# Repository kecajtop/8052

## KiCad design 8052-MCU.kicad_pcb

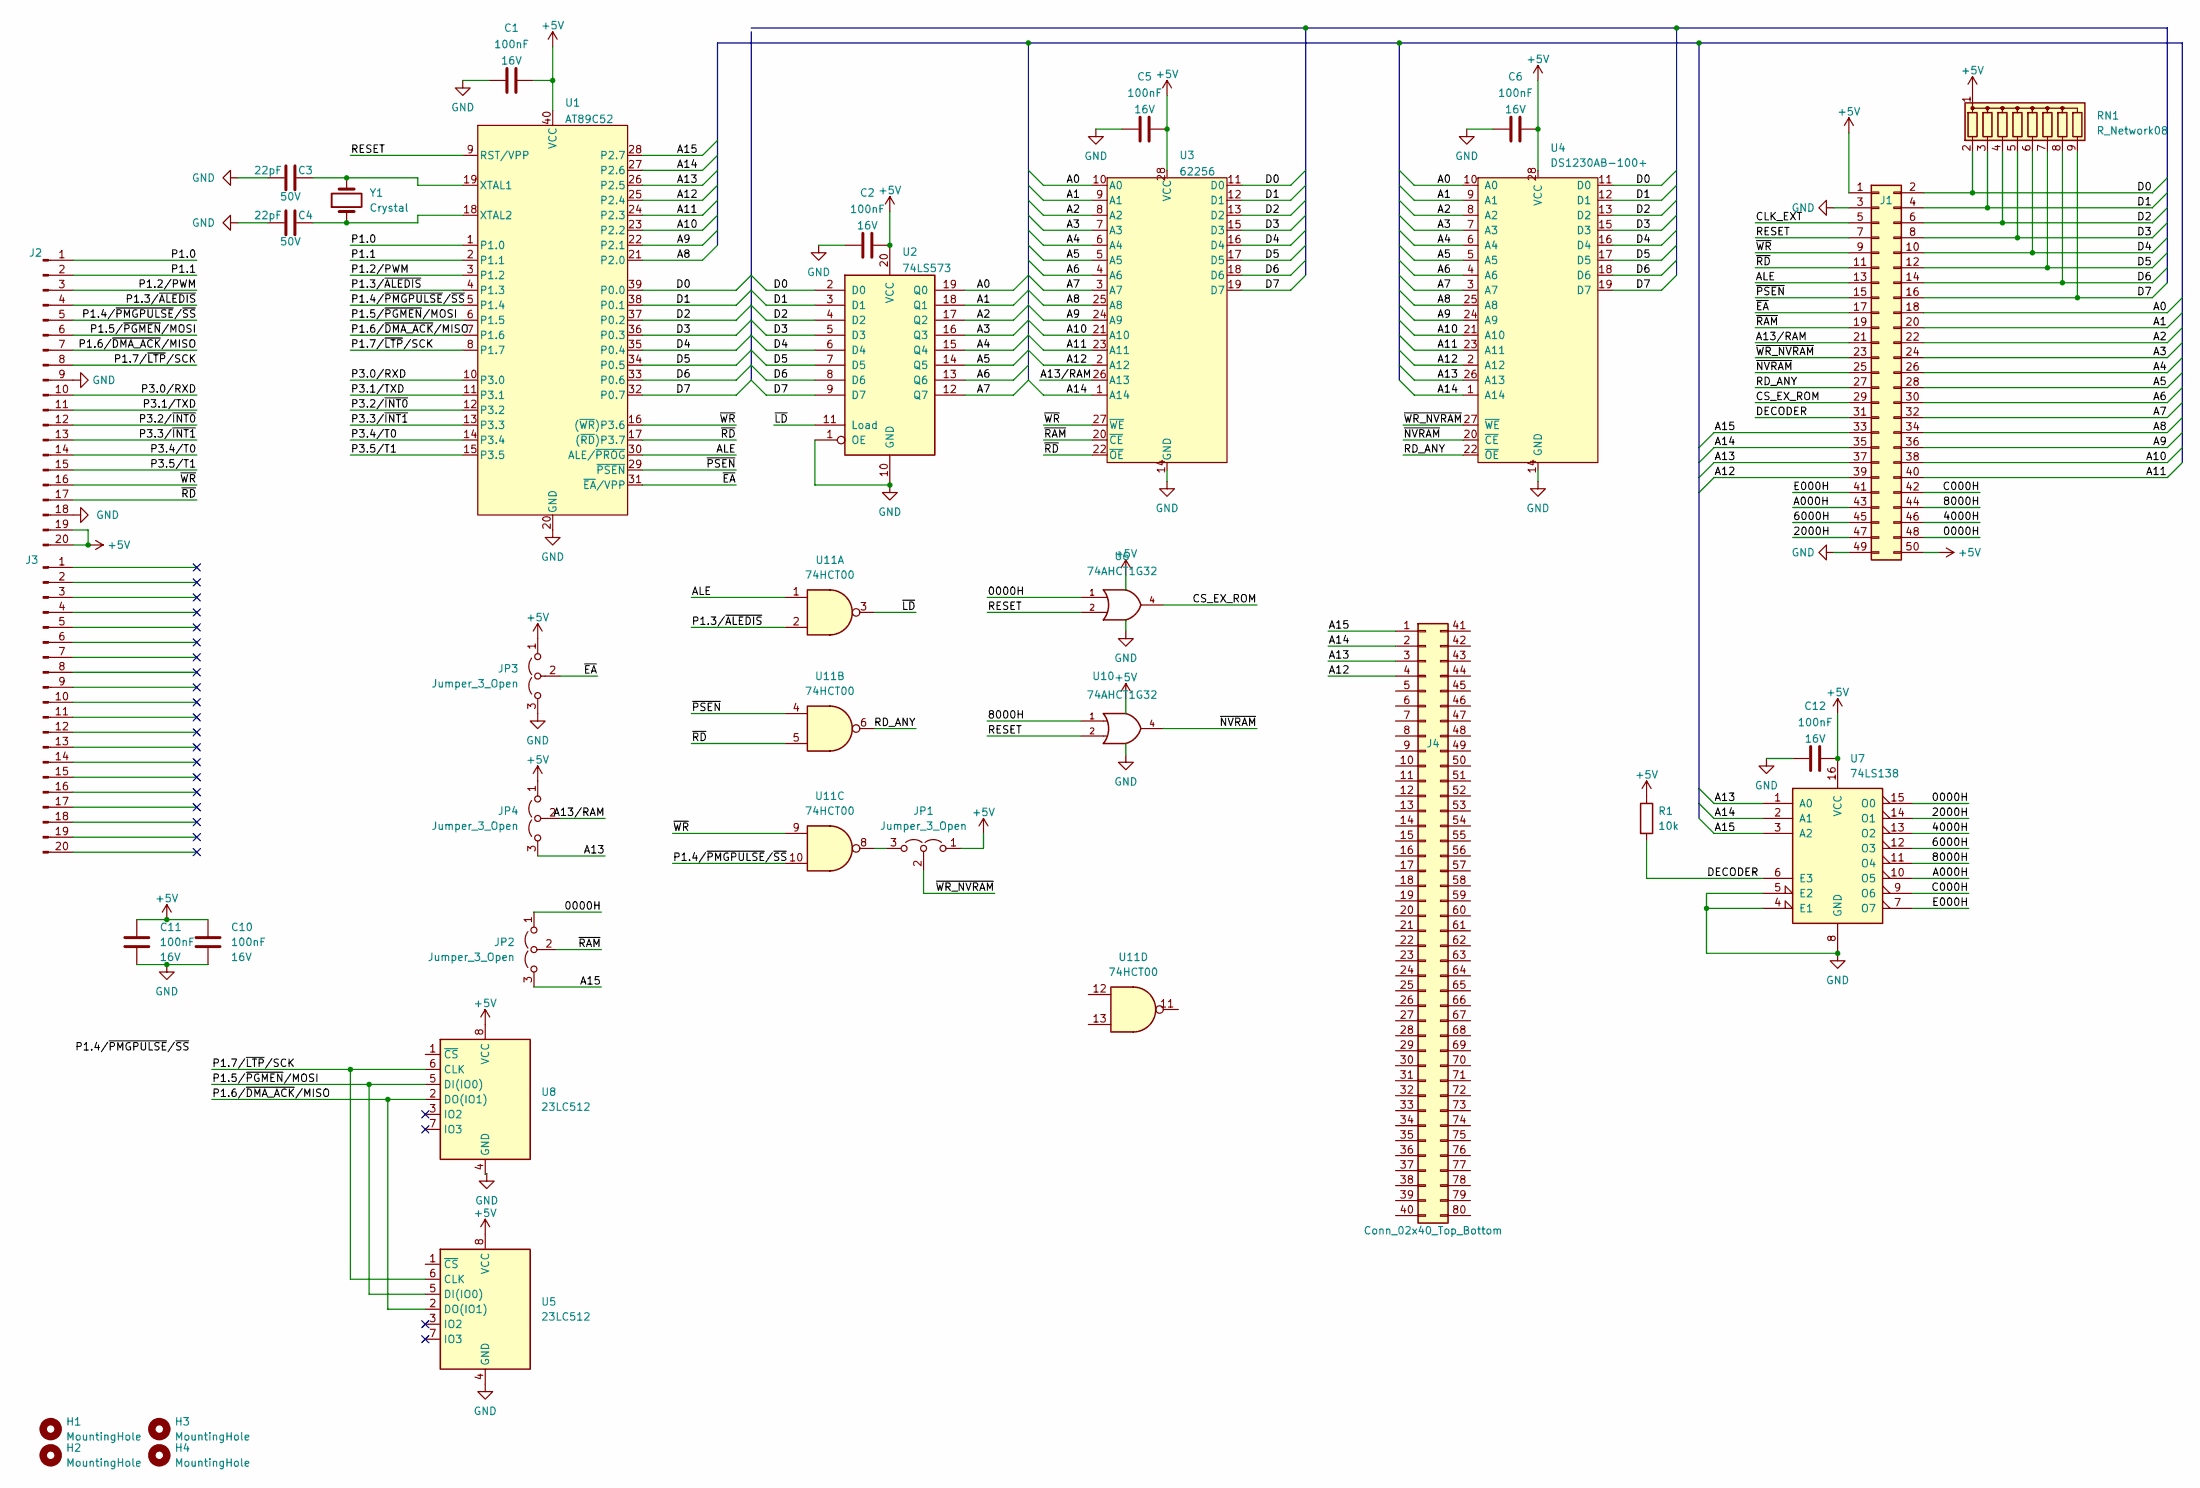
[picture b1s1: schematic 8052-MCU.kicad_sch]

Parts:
C1, C2, C5, C6, C10, C11, C12: C0805_100nF_16V_X7R; C_0805_2012Metric; Voltage 16V; Manufacturer Part Number C0805C104K4RACTU
C3, C4: C0603_22pF_50V_X7R; C_0603_1608Metric; Voltage 50V; Manufacturer Part Number C0603C220J5RAC7867
H1, H2, H3, H4: MountingHole; MountingHole_3.2mm_M3
J1: Conn_02x25_Odd_Even; PinHeader_2x25_P2.54mm_Vertical
J2, J3: Conn_01x20_Pin; PinHeader_1x20_P2.54mm_Vertical
J4: Conn_02x40_Top_Bottom; PinHeader_2x40_P2.54mm_Vertical
JP1, JP2, JP3, JP4: Jumper_3_Open; PinHeader_1x03_P2.54mm_Vertical
R1: R0805_10k_1%_125mW_100PPM_AC; R_0805_2012Metric; Manufacturer Part Number AC0805FR-0710KL
RN1: R_Network08; R_Array_SIP9
U1: AT89C52; DIP-40_W15.24mm_Socket_LongPads; Manufacturer Part Number AT89C52
U2: 74LS573; DIP-20_W7.62mm_Socket_LongPads
U3: 62256; DIP-28_W15.24mm_Socket_LongPads; Manufacturer Part Number 62256
U4: DS1230AB-100+; DIP-28_W15.24mm_Socket_LongPads
U5, U8: 23LC512; SOIC-8_3.9x4.9mm_P1.27mm
U6, U10: 74AHCT1G32; SOT-23-5
U7: 74LS138; SOIC-16_3.9x9.9mm_P1.27mm
U11: 74HCT00; SO-14_3.9x8.65mm_P1.27mm
Y1: Crystal; Crystal_HC49-U_Vertical

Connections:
+5V: C1.2, C2.2, C5.2, C6.2, C10.2, C11.2, C12.2, J1.1, J1.50, J2.19, J2.20, JP1.1 (A), JP3.1 (A), JP4.1 (A), R1.1, RN1.1 (common), U1.40 (VCC), U2.20 (VCC), U3.28 (VCC), U4.28 (VCC), U5.8 (VCC), U6.5 (VCC), U7.16 (VCC), U8.8 (VCC), U10.5 (VCC)
/0000H: J1.48, JP2.1 (A), U6.1, U7.15 (O0)
/2000H: J1.47, U7.14 (O1)
/4000H: J1.46, U7.13 (O2)
/6000H: J1.45, U7.12 (O3)
/8000H: J1.44, U7.11 (O4), U10.1
/A0: J1.18, U2.19 (Q0), U3.10 (A0), U4.10 (A0)
/A000H: J1.43, U7.10 (O5)
/A1: J1.20, U2.18 (Q1), U3.9 (A1), U4.9 (A1)
/A2: J1.22, U2.17 (Q2), U3.8 (A2), U4.8 (A2)
/A3: J1.24, U2.16 (Q3), U3.7 (A3), U4.7 (A3)
/A4: J1.26, U2.15 (Q4), U3.6 (A4), U4.6 (A4)
/A5: J1.28, U2.14 (Q5), U3.5 (A5), U4.5 (A5)
/A6: J1.30, U2.13 (Q6), U3.4 (A6), U4.4 (A6)
/A7: J1.32, U2.12 (Q7), U3.3 (A7), U4.3 (A7)
/A8: J1.34, U1.21 (P2.0), U3.25 (A8), U4.25 (A8)
/A9: J1.36, U1.22 (P2.1), U3.24 (A9), U4.24 (A9)
/A10: J1.38, U1.23 (P2.2), U3.21 (A10), U4.21 (A10)
/A11: J1.40, U1.24 (P2.3), U3.23 (A11), U4.23 (A11)
/A12: J1.39, J4.4, U1.25 (P2.4), U3.2 (A12), U4.2 (A12)
/A13: J1.37, J4.3, JP4.3 (B), U1.26 (P2.5), U4.26 (A13), U7.1 (A0)
/A13/RAM: J1.21, JP4.2 (C), U3.26 (A13)
/A14: J1.35, J4.2, U1.27 (P2.6), U3.1 (A14), U4.1 (A14), U7.2 (A1)
/A15: J1.33, J4.1, JP2.3 (B), U1.28 (P2.7), U7.3 (A2)
/ALE: J1.13, U1.30 (ALE/~PROG), U11.1
/C000H: J1.42, U7.9 (O6)
/CLK_EXT: J1.5
/CS_EX_ROM: J1.29, U6.4
/D0: J1.2, RN1.2 (R1), U1.39 (P0.0), U2.2 (D0), U3.11 (D0), U4.11 (D0)
/D1: J1.4, RN1.3 (R2), U1.38 (P0.1), U2.3 (D1), U3.12 (D1), U4.12 (D1)
/D2: J1.6, RN1.4 (R3), U1.37 (P0.2), U2.4 (D2), U3.13 (D2), U4.13 (D2)
/D3: J1.8, RN1.5 (R4), U1.36 (P0.3), U2.5 (D3), U3.15 (D3), U4.15 (D3)
/D4: J1.10, RN1.6 (R5), U1.35 (P0.4), U2.6 (D4), U3.16 (D4), U4.16 (D4)
/D5: J1.12, RN1.7 (R6), U1.34 (P0.5), U2.7 (D5), U3.17 (D5), U4.17 (D5)
/D6: J1.14, RN1.8 (R7), U1.33 (P0.6), U2.8 (D6), U3.18 (D6), U4.18 (D6)
/D7: J1.16, RN1.9 (R8), U1.32 (P0.7), U2.9 (D7), U3.19 (D7), U4.19 (D7)
/DECODER: J1.31, R1.2, U7.6 (E3)
/E000H: J1.41, U7.7 (O7)
/P1.0: J2.1, U1.1 (P1.0)
/P1.1: J2.2, U1.2 (P1.1)
/P1.2/PWM: J2.3, U1.3 (P1.2)
/P1.3/~ALEDIS: J2.4, U1.4 (P1.3), U11.2
/P1.4/~PMGPULSE/~SS: J2.5, U1.5 (P1.4), U11.10
/P1.5/~PGMEN/MOSI: J2.6, U1.6 (P1.5), U5.5 (DI(IO0)), U8.5 (DI(IO0))
/P1.6/~DMA_ACK/MISO: J2.7, U1.7 (P1.6), U5.2 (DO(IO1)), U8.2 (DO(IO1))
/P1.7/~LTP/SCK: J2.8, U1.8 (P1.7), U5.6 (CLK), U8.6 (CLK)
/P3.0/RXD: J2.10, U1.10 (P3.0)
/P3.1/TXD: J2.11, U1.11 (P3.1)
/P3.2/~INT0: J2.12, U1.12 (P3.2)
/P3.3/~INT1: J2.13, U1.13 (P3.3)
/P3.4/T0: J2.14, U1.14 (P3.4)
/P3.5/T1: J2.15, U1.15 (P3.5)
/RD_ANY: J1.27, U4.22 (~OE), U11.6
/RESET: J1.7, U1.9 (RST/VPP), U6.2, U10.2
/~EA: J1.17, JP3.2 (C), U1.31 (~EA/VPP)
/~LD: U2.11 (Load), U11.3
/~NVRAM: J1.25, U4.20 (~CE), U10.4
/~PSEN: J1.15, U1.29 (~PSEN), U11.4
/~RAM: J1.19, JP2.2 (C), U3.20 (~CE)
/~RD: J1.11, J2.17, U1.17 ((~RD)P3.7), U3.22 (~OE), U11.5
/~WR_NVRAM: J1.23, JP1.2 (C), U4.27 (~WE)
/~WR: J1.9, J2.16, U1.16 ((~WR)P3.6), U3.27 (~WE), U11.9
GND: C1.1, C2.1, C3.1, C4.1, C5.1, C6.1, C10.1, C11.1, C12.1, J1.3, J1.49, J2.9, J2.18, JP3.3 (B), U1.20 (GND), U2.1 (OE), U2.10 (GND), U3.14 (GND), U4.14 (GND), U5.4 (GND), U6.3 (GND), U7.4 (E1), U7.5 (E2), U7.8 (GND), U8.4 (GND), U10.3 (GND)
unnamed: JP1.3 (B), U11.8
unnamed: C3.2, U1.19 (XTAL1), Y1.2
unnamed: C4.2, U1.18 (XTAL2), Y1.1

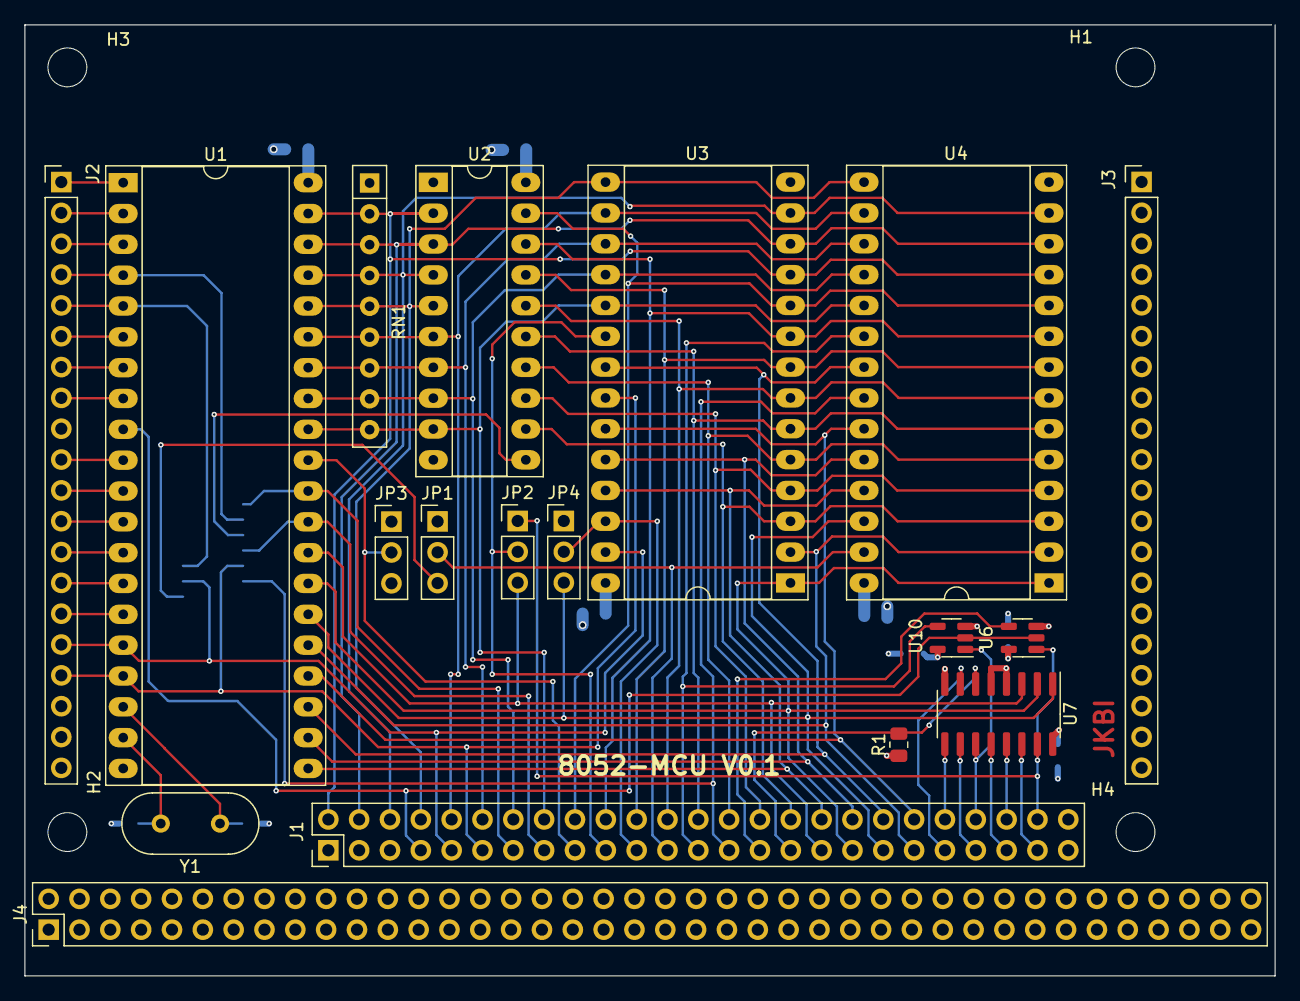
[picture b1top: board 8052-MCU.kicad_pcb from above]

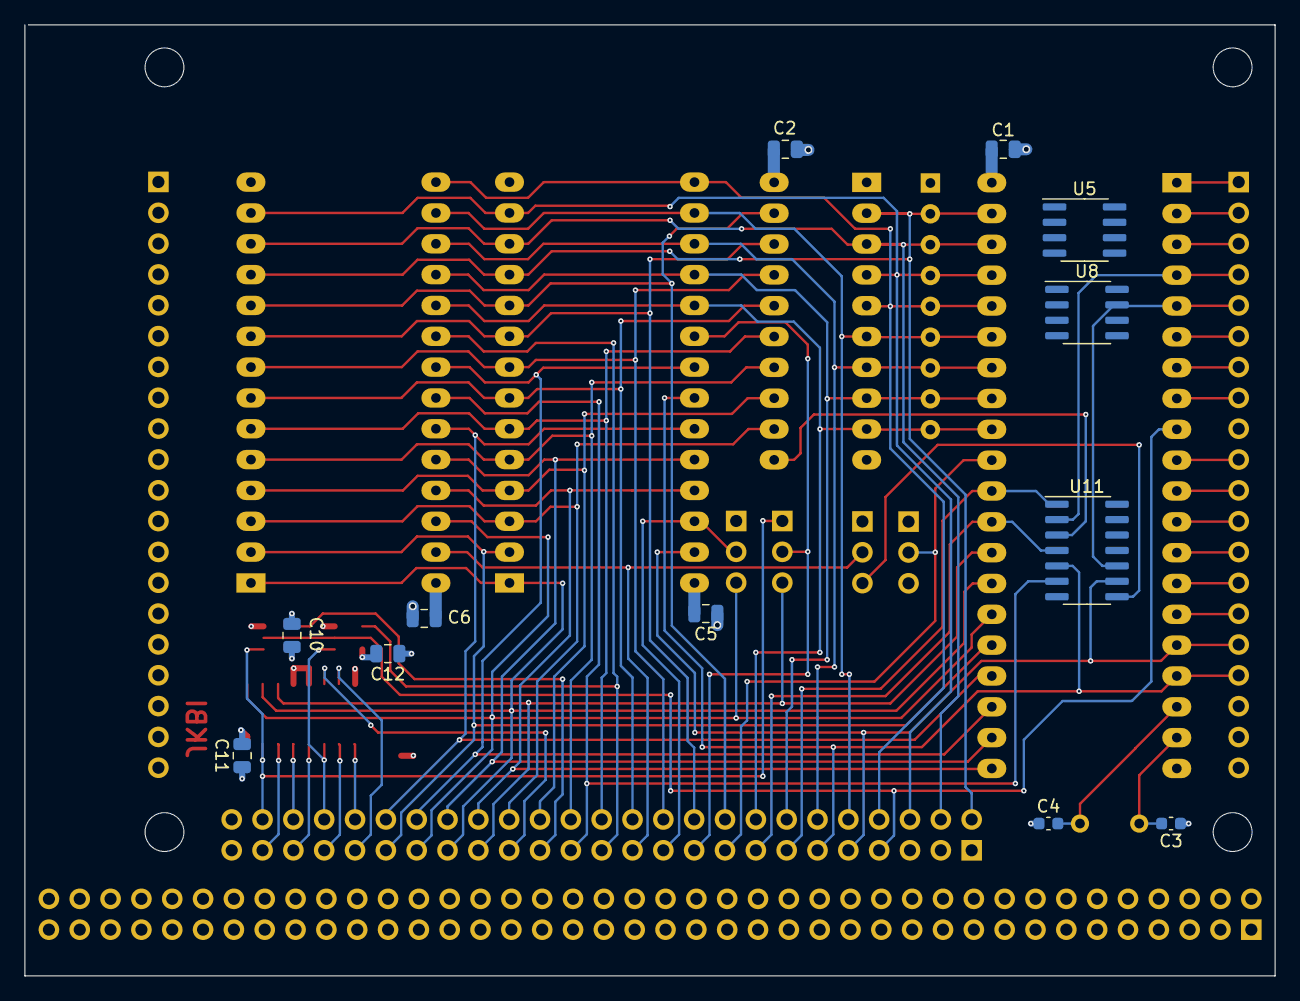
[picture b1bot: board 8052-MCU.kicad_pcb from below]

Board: 4 copper layers, 103.0 x 78.3 mm, 34 parts (12 on the bottom side), 65 nets.

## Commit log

2023-09-16 making layout changes
2023-10-02 Renamed
